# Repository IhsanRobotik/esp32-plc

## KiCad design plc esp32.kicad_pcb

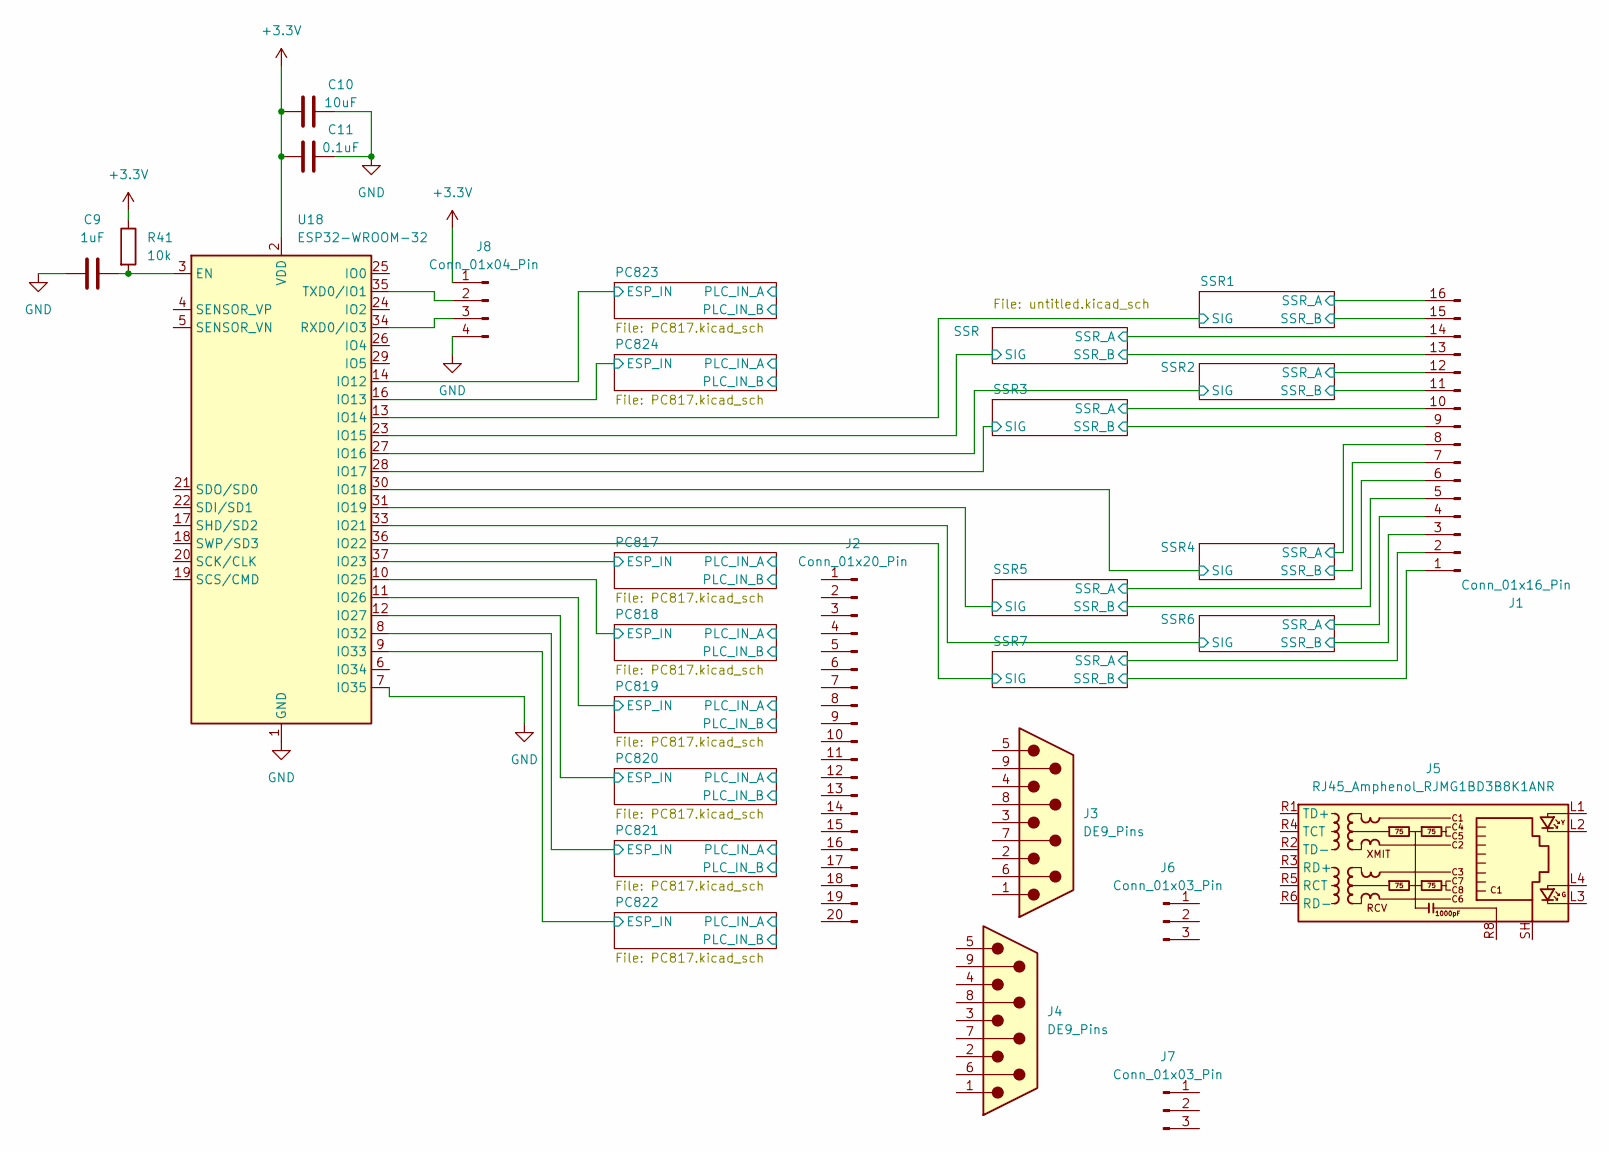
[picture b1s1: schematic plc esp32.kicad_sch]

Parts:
C9: 1uF; C_Disc_D5.0mm_W2.5mm_P5.00mm
C10: 10uF; CP_Radial_D5.0mm_P2.50mm
C11: 0.1uF; C_Rect_L7.0mm_W2.5mm_P5.00mm
J1: Conn_01x16_Pin; 8x2terminal
J2: Conn_01x20_Pin; 10x2 with screw
J3, J4: DE9_Pins; DSUB-9_Pins_Vertical_P2.77x2.84mm
J5: RJ45_Amphenol_RJMG1BD3B8K1ANR
J6, J7: Conn_01x03_Pin; PhoenixContact_MC_1,5_3-G-5.08_1x03_P5.08mm_Horizontal
J8: Conn_01x04_Pin; JST_XH_B4B-XH-A_1x04_P2.50mm_Vertical
R41: 10k; R_Axial_DIN0207_L6.3mm_D2.5mm_P7.62mm_Horizontal
U18: ESP32-WROOM-32

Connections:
+3.3V: C10.1, C11.1, J8.1, R41.1, U18.2 (VDD); also elsewhere on the board
/PC817/ESP_IN: U18.37 (IO23); also elsewhere on the board
/PC818/ESP_IN: U18.10 (IO25); also elsewhere on the board
/PC819/ESP_IN: U18.11 (IO26); also elsewhere on the board
/PC820/ESP_IN: U18.12 (IO27); also elsewhere on the board
/PC821/ESP_IN: U18.8 (IO32); also elsewhere on the board
/PC822/ESP_IN: U18.9 (IO33); also elsewhere on the board
/PC823/ESP_IN: U18.14 (IO12); also elsewhere on the board
/PC824/ESP_IN: U18.16 (IO13); also elsewhere on the board
/SSR1/SIG: U18.13 (IO14); also elsewhere on the board
/SSR1/SSR_A: J1.16; also elsewhere on the board
/SSR1/SSR_B: J1.15; also elsewhere on the board
/SSR2/SIG: U18.27 (IO16); also elsewhere on the board
/SSR2/SSR_A: J1.12; also elsewhere on the board
/SSR2/SSR_B: J1.11; also elsewhere on the board
/SSR3/SIG: U18.28 (IO17); also elsewhere on the board
/SSR3/SSR_A: J1.10; also elsewhere on the board
/SSR3/SSR_B: J1.9; also elsewhere on the board
/SSR4/SIG: U18.30 (IO18); also elsewhere on the board
/SSR4/SSR_A: J1.8; also elsewhere on the board
/SSR4/SSR_B: J1.7; also elsewhere on the board
/SSR5/SIG: U18.31 (IO19); also elsewhere on the board
/SSR5/SSR_A: J1.6; also elsewhere on the board
/SSR5/SSR_B: J1.5; also elsewhere on the board
/SSR6/SIG: U18.33 (IO21); also elsewhere on the board
/SSR6/SSR_A: J1.4; also elsewhere on the board
/SSR6/SSR_B: J1.3; also elsewhere on the board
/SSR7/SIG: U18.36 (IO22); also elsewhere on the board
/SSR7/SSR_A: J1.2; also elsewhere on the board
/SSR7/SSR_B: J1.1; also elsewhere on the board
/SSR/SIG: U18.23 (IO15); also elsewhere on the board
/SSR/SSR_A: J1.14; also elsewhere on the board
/SSR/SSR_B: J1.13; also elsewhere on the board
GND: C9.1, C10.2, C11.2, J8.4, U18.1 (GND), U18.7 (IO35), U18.15 (GND), U18.38 (GND), U18.39 (GND); also elsewhere on the board
unnamed: J8.2, U18.35 (TXD0/IO1)
unnamed: J8.3, U18.34 (RXD0/IO3)
unnamed: C9.2, R41.2, U18.3 (EN)

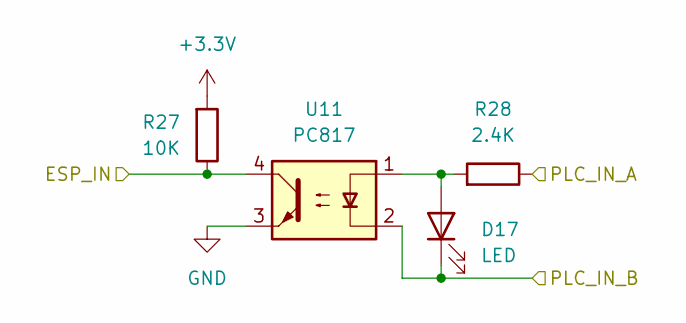
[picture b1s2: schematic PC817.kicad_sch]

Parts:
D17: LED; LED_D3.0mm
R27: 10K; R_Axial_DIN0207_L6.3mm_D2.5mm_P7.62mm_Horizontal
R28: 2.4K; R_Axial_DIN0207_L6.3mm_D2.5mm_P7.62mm_Horizontal
U11: PC817; DIP-4_W7.62mm

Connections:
+3.3V: R27.2; also elsewhere on the board
/PC817/ESP_IN: R27.1, U11.4; also elsewhere on the board
/PC817/PLC_IN_A: R28.1
/PC817/PLC_IN_B: D17.1 (K), U11.2
GND: U11.3; also elsewhere on the board
unnamed: D17.2 (A), R28.2, U11.1

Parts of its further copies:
D18, D19, D20, D21, D22, D23, D24: LED; LED_D3.0mm
R25, R29, R31, R33, R35, R37, R39: 10K; R_Axial_DIN0207_L6.3mm_D2.5mm_P7.62mm_Horizontal
R26, R30, R32, R34, R36, R38, R40: 2.4K; R_Axial_DIN0207_L6.3mm_D2.5mm_P7.62mm_Horizontal
U10, U12, U13, U14, U15, U16, U17: PC817; DIP-4_W7.62mm

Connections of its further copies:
+3.3V: R25.2, R29.2, R31.2, R33.2, R35.2, R37.2, R39.2; also elsewhere on the board
/PC818/ESP_IN: R25.1, U10.4; also elsewhere on the board
/PC818/PLC_IN_A: R26.1
/PC818/PLC_IN_B: D18.1 (K), U10.2
/PC819/ESP_IN: R29.1, U12.4; also elsewhere on the board
/PC819/PLC_IN_A: R30.1
/PC819/PLC_IN_B: D19.1 (K), U12.2
/PC820/ESP_IN: R31.1, U13.4; also elsewhere on the board
/PC820/PLC_IN_A: R32.1
/PC820/PLC_IN_B: D20.1 (K), U13.2
/PC821/ESP_IN: R33.1, U14.4; also elsewhere on the board
/PC821/PLC_IN_A: R34.1
/PC821/PLC_IN_B: D21.1 (K), U14.2
/PC822/ESP_IN: R35.1, U15.4; also elsewhere on the board
/PC822/PLC_IN_A: R36.1
/PC822/PLC_IN_B: D22.1 (K), U15.2
/PC823/ESP_IN: R37.1, U16.4; also elsewhere on the board
/PC823/PLC_IN_A: R38.1
/PC823/PLC_IN_B: D23.1 (K), U16.2
/PC824/ESP_IN: R39.1, U17.4; also elsewhere on the board
/PC824/PLC_IN_A: R40.1
/PC824/PLC_IN_B: D24.1 (K), U17.2
GND: U10.3, U12.3, U13.3, U14.3, U15.3, U16.3, U17.3; also elsewhere on the board
unnamed: D18.2 (A), R26.2, U10.1
unnamed: D19.2 (A), R30.2, U12.1
unnamed: D20.2 (A), R32.2, U13.1
unnamed: D21.2 (A), R34.2, U14.1
unnamed: D22.2 (A), R36.2, U15.1
unnamed: D23.2 (A), R38.2, U16.1
unnamed: D24.2 (A), R40.2, U17.1

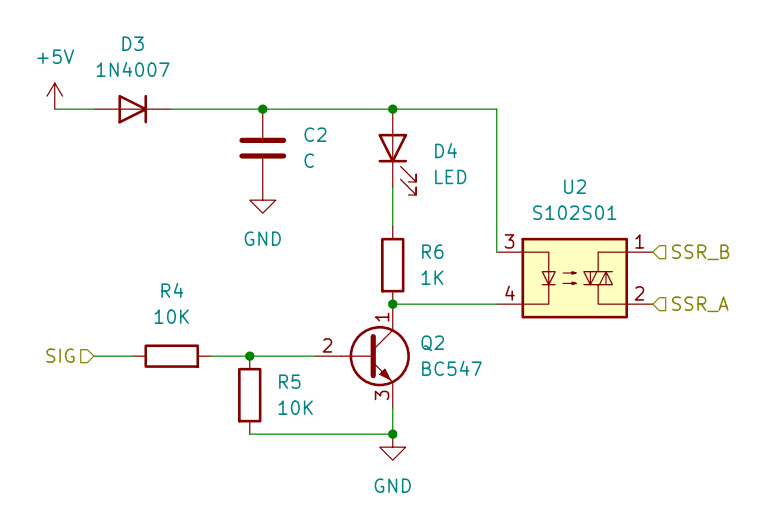
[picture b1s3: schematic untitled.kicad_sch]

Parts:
C2: C; C_Disc_D5.0mm_W2.5mm_P2.50mm
D3: 1N4007; D_DO-41_SOD81_P10.16mm_Horizontal
D4: LED; LED_D3.0mm
Q2: BC547; TO-92_Inline
R4, R5: 10K; R_Axial_DIN0207_L6.3mm_D2.5mm_P7.62mm_Horizontal
R6: 1K; R_Axial_DIN0207_L6.3mm_D2.5mm_P7.62mm_Horizontal
U2: S102S01; RELAY_G3MB-202P

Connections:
+5V: D3.2 (A); also elsewhere on the board
/SSR/SIG: R4.1; also elsewhere on the board
/SSR/SSR_A: U2.2; also elsewhere on the board
/SSR/SSR_B: U2.1; also elsewhere on the board
GND: C2.2, Q2.3 (E), R5.2; also elsewhere on the board
unnamed: C2.1, D3.1 (K), D4.2 (A), U2.3
unnamed: D4.1 (K), R6.1
unnamed: Q2.2 (B), R4.2, R5.1
unnamed: Q2.1 (C), R6.2, U2.4

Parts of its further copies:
C1, C3, C4, C5, C6, C7, C8: C; C_Disc_D5.0mm_W2.5mm_P2.50mm
D1, D5, D7, D9, D11, D13, D15: 1N4007; D_DO-41_SOD81_P10.16mm_Horizontal
D2, D6, D8, D10, D12, D14, D16: LED; LED_D3.0mm
Q1, Q3, Q4, Q5, Q6, Q7, Q8: BC547; TO-92_Inline
R1, R2, R7, R8, R10, R11, R13, R14, R16, R17, R19, R20, R22, R23: 10K; R_Axial_DIN0207_L6.3mm_D2.5mm_P7.62mm_Horizontal
R3, R9, R12, R15, R18, R21, R24: 1K; R_Axial_DIN0207_L6.3mm_D2.5mm_P7.62mm_Horizontal
U1, U3, U4, U5, U6, U7, U8: S102S01; RELAY_G3MB-202P

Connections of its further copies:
+5V: D1.2 (A), D5.2 (A), D7.2 (A), D9.2 (A), D11.2 (A), D13.2 (A), D15.2 (A); also elsewhere on the board
/SSR1/SIG: R1.1; also elsewhere on the board
/SSR1/SSR_A: U1.2; also elsewhere on the board
/SSR1/SSR_B: U1.1; also elsewhere on the board
/SSR2/SIG: R7.1; also elsewhere on the board
/SSR2/SSR_A: U3.2; also elsewhere on the board
/SSR2/SSR_B: U3.1; also elsewhere on the board
/SSR3/SIG: R10.1; also elsewhere on the board
/SSR3/SSR_A: U4.2; also elsewhere on the board
/SSR3/SSR_B: U4.1; also elsewhere on the board
/SSR4/SIG: R13.1; also elsewhere on the board
/SSR4/SSR_A: U5.2; also elsewhere on the board
/SSR4/SSR_B: U5.1; also elsewhere on the board
/SSR5/SIG: R16.1; also elsewhere on the board
/SSR5/SSR_A: U6.2; also elsewhere on the board
/SSR5/SSR_B: U6.1; also elsewhere on the board
/SSR6/SIG: R19.1; also elsewhere on the board
/SSR6/SSR_A: U7.2; also elsewhere on the board
/SSR6/SSR_B: U7.1; also elsewhere on the board
/SSR7/SIG: R22.1; also elsewhere on the board
/SSR7/SSR_A: U8.2; also elsewhere on the board
/SSR7/SSR_B: U8.1; also elsewhere on the board
GND: C1.2, C3.2, C4.2, C5.2, C6.2, C7.2, C8.2, Q1.3 (E), Q3.3 (E), Q4.3 (E), Q5.3 (E), Q6.3 (E), Q7.3 (E), Q8.3 (E), R2.2, R8.2, R11.2, R14.2, R17.2, R20.2, R23.2; also elsewhere on the board
unnamed: C1.1, D1.1 (K), D2.2 (A), U1.3
unnamed: D2.1 (K), R3.1
unnamed: C3.1, D5.1 (K), D6.2 (A), U3.3
unnamed: D6.1 (K), R9.1
unnamed: C4.1, D7.1 (K), D8.2 (A), U4.3
unnamed: D8.1 (K), R12.1
unnamed: C5.1, D9.1 (K), D10.2 (A), U5.3
unnamed: D10.1 (K), R15.1
unnamed: C6.1, D11.1 (K), D12.2 (A), U6.3
unnamed: D12.1 (K), R18.1
unnamed: C7.1, D13.1 (K), D14.2 (A), U7.3
unnamed: D14.1 (K), R21.1
unnamed: C8.1, D15.1 (K), D16.2 (A), U8.3
unnamed: D16.1 (K), R24.1
unnamed: Q1.2 (B), R1.2, R2.1
unnamed: Q1.1 (C), R3.2, U1.4
unnamed: Q3.2 (B), R7.2, R8.1
unnamed: Q3.1 (C), R9.2, U3.4
unnamed: Q4.2 (B), R10.2, R11.1
unnamed: Q4.1 (C), R12.2, U4.4
unnamed: Q5.2 (B), R13.2, R14.1
unnamed: Q5.1 (C), R15.2, U5.4
unnamed: Q6.2 (B), R16.2, R17.1
unnamed: Q6.1 (C), R18.2, U6.4
unnamed: Q7.2 (B), R19.2, R20.1
unnamed: Q7.1 (C), R21.2, U7.4
unnamed: Q8.2 (B), R22.2, R23.1
unnamed: Q8.1 (C), R24.2, U8.4

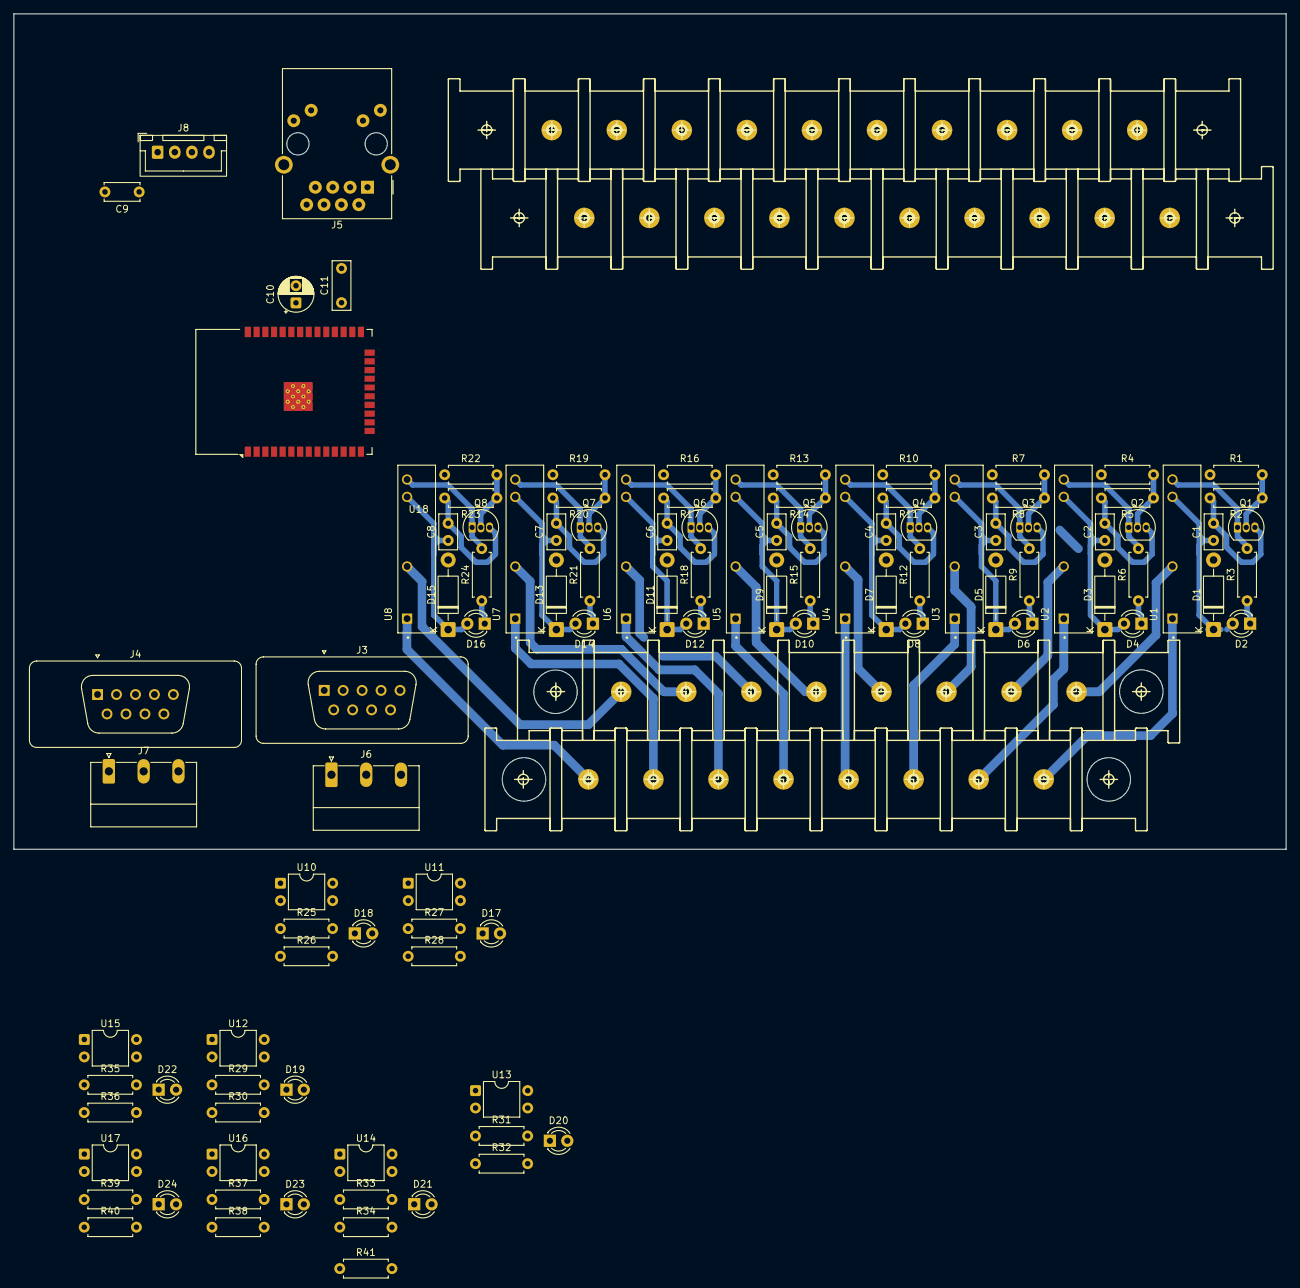
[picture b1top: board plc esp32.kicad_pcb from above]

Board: 2 copper layers, 185.8 x 122.0 mm, 109 parts (0 on the bottom side), 86 nets.
